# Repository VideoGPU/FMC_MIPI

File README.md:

# FMC_MIPI
FMC card to allow interfacing Xilinx FPGA boards with Jetson TX2 or TX1 via CSI-2 camera interface.
Made with KiCad.
Tested and works fine with KC705

HS and LP lanes come as a separate lines from FPGA.Switching between HS and LP modes is done using a high-speed switch 
TS3DDR3812.

## Some pictures:
Terminal output:

Example output:
The vertical line position in magenta strip indicates a frame number

The whole setup:

Interconnector board:

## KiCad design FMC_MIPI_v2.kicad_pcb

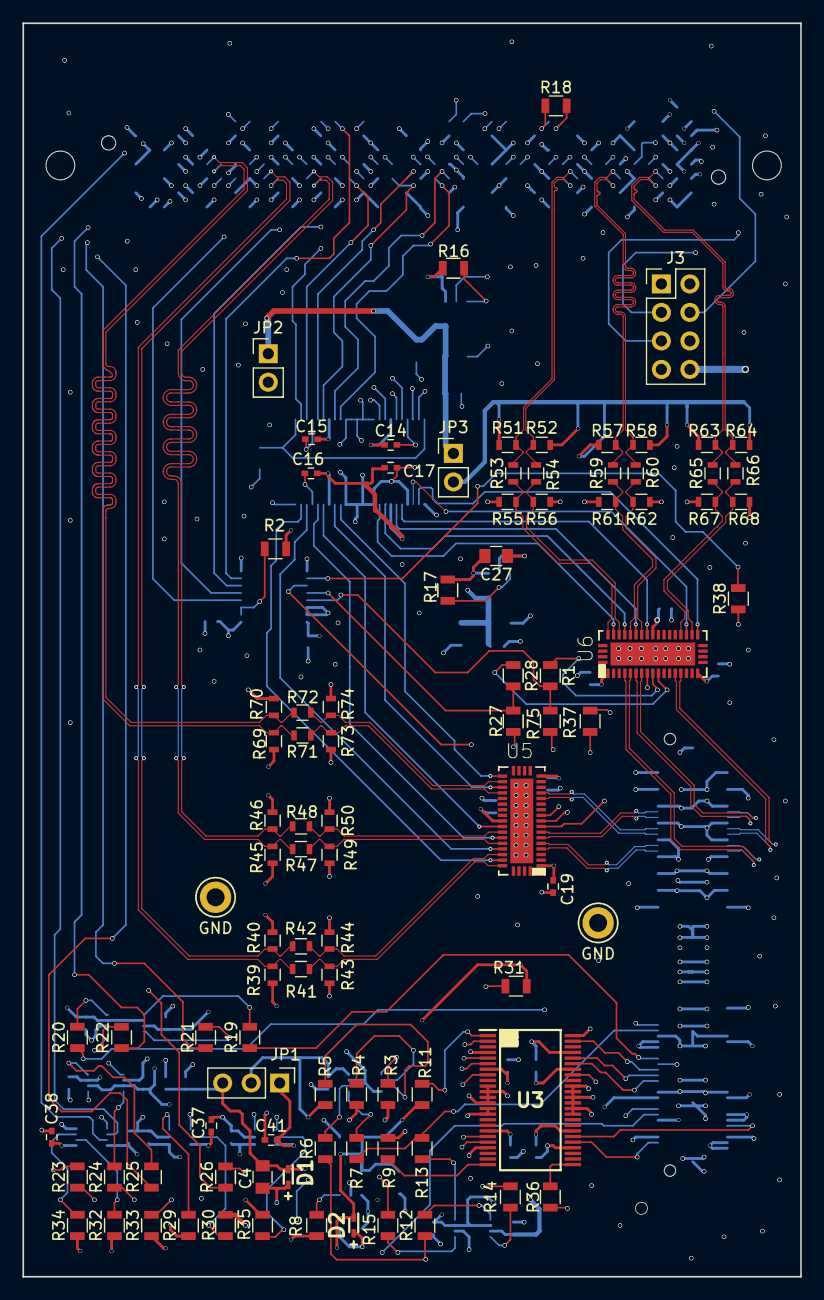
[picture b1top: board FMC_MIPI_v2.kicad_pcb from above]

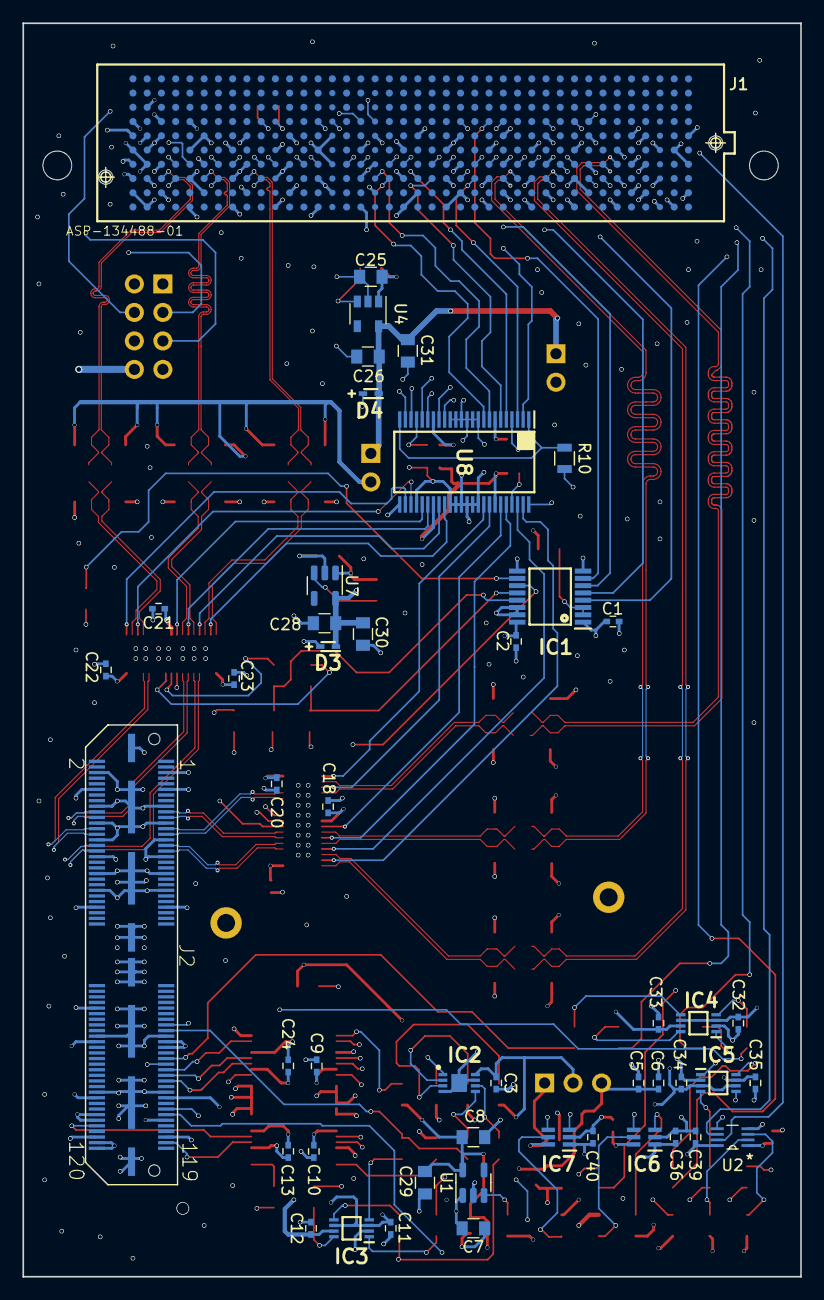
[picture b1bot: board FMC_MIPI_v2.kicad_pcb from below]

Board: 6 copper layers, 69.3 x 111.8 mm, 143 parts (48 on the bottom side), 156 nets.

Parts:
C1, C2, C3, C5, C6, C9, C10, C11, C12, C13, C14, C15, C16, C17, C18, C19, C20, C21, C22, C23, C24, C32, C33, C34, C35, C36, C37, C38, C39, C40, C41: 0.1uF; C_0402
C4, C29, C30, C31: 4.7uF; C_0805
C7, C8, C25, C26, C27, C28: 1uF; C_0805
D1, D2, D3, D4: UCLAMP0501H.TCT; SODFL1608X70N
IC1: SN74AVC4T245PWR; SOP65P640X120-16N
IC2: AT24MAC402-MAHM-T; SON50P300X200X60-9N
IC3, IC4, IC5: TCA9406DCUR; SOP50P310X90-8N
IC6, IC7: SN74AVC1T45DCKT; SOT65P210X110-6N
J1: ASP-134488-01; ASP-134488-01_VER2
J2: QTH-060-01-L-D-A; QTH-060-01-X-D-A-QTH-060-01-X-D-A
J3: Conn_01x08_Female; PinHeader_2x04_P2.54mm_Vertical
JP1: Jumper_3_Bridged12; Pin_Header_Straight_1x03_Pitch2.54mm
JP2, JP3: Jumper; Pin_Header_Straight_1x02_Pitch2.54mm
R1, R6, R7, R8, R12, R13, R14, R15, R16, R17, R18, R19, R20, R21, R22, R23, R24, R25, R26, R27, R28, R36, R37, R38, R75: 0; R_0805
R2, R3, R4, R5, R9, R10, R11, R30, R33, R35: 4.7k; R_0805
R29, R31, R32, R34: 2.2k; R_0805
R39, R40, R45, R46, R51, R52, R57, R58, R63, R64, R69, R70: 220; R_0603
R41, R42, R47, R48, R53, R54, R59, R60, R65, R66, R71, R72: 47; R_0603
R43, R44, R49, R50, R55, R56, R61, R62, R67, R68, R73, R74: 9.1; R_0603
TP1, TP2: GND; TestPoint_Keystone_5010-5014_Multipurpose
U1: LP5907MFX-1.8; SOT-23-5
U2: SN74AVC2T45DCUR
U3, U8: SN74AVCH16T245GR; SOP50P810X120-48N
U4: TLV75525PDBV; SOT-23-5
U5, U6: TS3DDR3812_RUA_42; TS3DDR3812RUAR
U7: LP5907MFX-1.2; SOT-23-5

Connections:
/FMC_Connector/DBG_IO_1: J1.G34 (LA31_N), J3.1
/FMC_Connector/DBG_IO_2: J1.G37 (LA33_N), J3.2
/FMC_Connector/DBG_IO_3: J1.G36 (LA33_P), J3.3
/FMC_Connector/DBG_IO_4: J1.G31 (LA29_N), J3.4
/FMC_Connector/DBG_IO_5: J1.D24 (LA23_N), J3.5
/FMC_Connector/DBG_IO_6: J1.D23 (LA23_P), J3.6
/FMC_Connector/TDI: J1.D30 (TDI), R18.1
/FMC_Connector/TDO: J1.D31 (TDO), R18.2
/Jetson_connector/EEPROM_A0: IC2.1 (A0), R3.1
/Jetson_connector/EEPROM_A1: IC2.2 (A1), R4.1
/Jetson_connector/EEPROM_A2: IC2.3 (A2), R5.1
/Jetson_connector/EEPROM_SCL: IC2.6 (SCL), R6.1
/Jetson_connector/EEPROM_SDA: IC2.5 (SDA), R7.1
/Jetson_connector/JT_VDD_1V2: J2.101 (DVDD_CAM_IO_1V2), R29.1
/Jetson_connector/JT_VDD_2V8: J2.81 (AVDD_CAM), J2.82 (AVDD_CAM), J2.83 (AVDD_CAM), R32.1
/Jetson_connector/JT_VDD_3V3: J2.108 (VDD_3V3_SLP1), J2.110 (VDD_3V3_SLP2), R34.1
/Jetson_connector/JT_VDD_5V: J2.109 (VDD_5V), J2.118 (VDD_5V), J2.120 (VDD_5V)
/Jetson_connector/VCC_1V8_EEPROM: C3.1, IC2.8 (VCC), JP1.2 (C), R5.2
/LVDS_to_Jetson_lines/CSI_LP_C_CLK_N: U5.24 (C8), U8.41 (1A5)
/LVDS_to_Jetson_lines/CSI_LP_C_CLK_P: U5.22 (C9), U8.40 (1A6)
/LVDS_to_Jetson_lines/CSI_LP_C_D0_N: U5.33 (C4), U8.44 (1A3)
/LVDS_to_Jetson_lines/CSI_LP_C_D0_P: U5.31 (C5), U8.43 (1A4)
/LVDS_to_Jetson_lines/CSI_LP_C_D1_N: U5.37 (C2), U8.47 (1A1)
/LVDS_to_Jetson_lines/CSI_LP_C_D1_P: U5.35 (C3), U8.46 (1A2)
/LVDS_to_Jetson_lines/CSI_LP_D_CLK_N: U6.24 (C8), U8.27 (2A7)
/LVDS_to_Jetson_lines/CSI_LP_D_CLK_P: U6.22 (C9), U8.26 (2A8)
/LVDS_to_Jetson_lines/CSI_LP_D_D0_N: U6.33 (C4), U8.30 (2A5)
/LVDS_to_Jetson_lines/CSI_LP_D_D0_P: U6.31 (C5), U8.29 (2A6)
/LVDS_to_Jetson_lines/CSI_LP_D_D1_N: U6.37 (C2), U8.33 (2A3)
/LVDS_to_Jetson_lines/CSI_LP_D_D1_P: U6.35 (C3), U8.32 (2A4)
/LVDS_to_Jetson_lines/DIR_IC1: IC1.2 (1DIR), IC1.3 (2DIR), R2.2
/LVDS_to_Jetson_lines/DIR_U8: R10.1, U8.1 (1DIR), U8.24 (2DIR)
/LVDS_to_Jetson_lines/EN_MIPI_OUT_CSI_C: IC1.11 (2B1), R37.2
/LVDS_to_Jetson_lines/EN_MIPI_OUT_CSI_D: IC1.10 (2B2), R38.2
/LVDS_to_Jetson_lines/EN_U5: R37.1, U5.8 (EN)
/LVDS_to_Jetson_lines/EN_U6: R38.1, U6.8 (EN)
/LVDS_to_Jetson_lines/HS_CSI_C_CLK_N: R71.1, R73.2, U5.25 (B8)
/LVDS_to_Jetson_lines/HS_CSI_C_CLK_P: R72.1, R74.1, U5.23 (B9)
/LVDS_to_Jetson_lines/HS_CSI_C_D0_N: R47.1, R49.2, U5.34 (B4)
/LVDS_to_Jetson_lines/HS_CSI_C_D0_P: R48.1, R50.1, U5.32 (B5)
/LVDS_to_Jetson_lines/HS_CSI_C_D1_N: R41.1, R43.2, U5.38 (B2)
/LVDS_to_Jetson_lines/HS_CSI_C_D1_P: R42.1, R44.1, U5.36 (B3)
/LVDS_to_Jetson_lines/HS_CSI_D_CLK_N: R65.1, R67.2, U6.25 (B8)
/LVDS_to_Jetson_lines/HS_CSI_D_CLK_P: R66.1, R68.1, U6.23 (B9)
/LVDS_to_Jetson_lines/HS_CSI_D_D0_N: R59.1, R61.2, U6.34 (B4)
/LVDS_to_Jetson_lines/HS_CSI_D_D0_P: R60.1, R62.1, U6.32 (B5)
/LVDS_to_Jetson_lines/HS_CSI_D_D1_N: R53.1, R55.2, U6.38 (B2)
/LVDS_to_Jetson_lines/HS_CSI_D_D1_P: R54.1, R56.1, U6.36 (B3)
/LVDS_to_Jetson_lines/SWITCH1_U5: R75.1, U5.9 (SEL1)
/LVDS_to_Jetson_lines/SWITCH1_U6: R1.1, U6.9 (SEL1)
/LVDS_to_Jetson_lines/SWITCH2_U5: R27.1, U5.10 (SEL2)
/LVDS_to_Jetson_lines/SWITCH2_U6: R28.1, U6.10 (SEL2)
/LVDS_to_Jetson_lines/SWITCH_CLOCK_LANES_CSI_CD: IC1.12 (1B2), R27.2, R28.2
/LVDS_to_Jetson_lines/SWITCH_DATA_LANES_CSI_CD: IC1.13 (1B1), R1.2, R75.2
/LVDS_to_Jetson_lines/VOLT_2P5_CSI_C: JP2.2, R39.1, R40.2, R45.1, R46.2, R69.1, R70.2
/LVDS_to_Jetson_lines/VOLT_2P5_CSI_D: JP3.2, R51.1, R52.2, R57.1, R58.2, R63.1, R64.2
/Slow_signals_level_shifters/1DIR_U3: R11.1, U3.1 (1DIR)
/Slow_signals_level_shifters/2DIR_U3: R9.1, U3.24 (2DIR)
/Slow_signals_level_shifters/ENN_JETSON_GPIO: IC7.4 (B), R36.2
/VDD_VADJ: C1.2, C9.1, C10.1, C12.1, C14.1, C15.1, C33.1, C35.1, C37.2, C39.2, C40.2, IC1.1 (VCCA), IC3.7 (VCCB), IC4.7 (VCCB), IC5.7 (VCCB), IC6.6 (VCCB), IC7.1 (VCCA), J1.E39 (VADJ), J1.F40 (VADJ), J1.G39 (VADJ), J1.H40 (VADJ), R2.1, R35.1, U2.8 (VCCB), U3.7 (VCCB_1), U3.18 (VCCB_2), U8.7 (VCCB_1), U8.18 (VCCB_2)
/VOLT_1P2: C16.1, C17.1, C28.2, C30.2, C36.2, D3.1, IC6.1 (VCCA), R30.1, U7.5 (OUT), U8.31 (VCCA_1), U8.42 (VCCA_2)
/VOLT_1P8: C8.2, C11.1, C13.1, C24.1, C29.2, C32.1, C34.1, C41.2, D2.1, IC3.3 (VCCA), IC3.6 (OE), IC4.3 (VCCA), IC4.6 (OE), IC5.3 (VCCA), IC5.6 (OE), IC7.6 (VCCB), JP1.1 (A), R11.2, U1.5 (OUT), U3.31 (VCCA_1), U3.42 (VCCA_2)
/VOLT_2P5: C26.2, C31.2, D4.1, JP2.1, JP3.1, U4.5 (OUT)
/VOLT_3P3: C2.2, C7.2, C18.2, C19.2, C20.2, C21.2, C22.2, C23.2, C25.2, C27.2, C38.2, IC1.16 (VCCB), J1.C39 (3PV3), J1.D36 (3P3V), J1.D38 (3P3V), J1.D40 (3P3V), R8.1, R16.1, R17.1, R33.1, U1.1 (IN), U2.1 (VCCA), U4.1 (IN), U5.1 (VCC), U5.17 (VCC), U5.30 (VCC), U6.1 (VCC), U6.17 (VCC), U6.30 (VCC), U7.1 (IN)
CSI_C_CLK_N: J2.27 (CSI2_CLK–), U5.13 (A8)
CSI_C_CLK_P: J2.25 (CSI2_CLK+), U5.14 (A9)
CSI_C_D0_N: J2.21 (CSI2_D0–), U5.6 (A4)
CSI_C_D0_P: J2.19 (CSI2_D0+), U5.7 (A5)
CSI_C_D1_N: J2.33 (CSI2_D1–), U5.4 (A2)
CSI_C_D1_P: J2.31 (CSI2_D1+), U5.5 (A3)
CSI_D_CLK_N: J2.28 (CSI3_CLK–), U6.13 (A8)
CSI_D_CLK_P: J2.26 (CSI3_CLK+), U6.14 (A9)
CSI_D_D0_N: J2.22 (CSI3_D0–), U6.6 (A4)
CSI_D_D0_P: J2.20 (CSI3_D0+), U6.7 (A5)
CSI_D_D1_N: J2.34 (CSI3_D1–), U6.4 (A2)
CSI_D_D1_P: J2.32 (CSI3_D1+), U6.5 (A3)
Earth: C1.1, C2.1, C3.2, C4.1, C5.1, C6.1, C7.1, C8.1, C9.2, C10.2, C11.2, C12.2, C13.2, C14.2, C15.2, C16.2, C17.2, C18.1, C19.1, C20.1, C21.1, C22.1, C23.1, C24.2, C25.1, C26.1, C27.1, C28.1, C29.1, C30.1, C31.1, C32.2, C33.2, C34.2, C35.2, C36.1, C37.1, C38.1, C39.1, C40.1, C41.1, D1.2, D2.2, D3.2, D4.2, IC1.8 (GND), IC1.9 (GND), IC1.14 (2~OE), IC1.15 (1~OE), IC2.4 (GND), IC2.7 (WP), IC2.9 (EP), IC3.2 (GND), IC4.2 (GND), IC5.2 (GND), IC6.2 (GND), IC7.2 (GND), J1.E1 (GND), J1.E4 (GND), J1.E5 (GND), J1.E8 (GND), J1.E11 (GND), J1.E14 (GND), J1.E17 (GND), J1.E20 (GND), J1.E23 (GND), J1.E26 (GND), J1.E29 (GND), J1.E32 (GND), J1.E35 (GND), J1.E38 (GND), J1.E40 (GND), J1.F2 (GND), J1.F3 (GND), J1.F6 (GND), J1.F9 (GND), J1.F12 (GND), J1.F15 (GND), J1.F18 (GND), J1.F21 (GND), J1.F24 (GND), J1.F27 (GND), J1.F30 (GND), J1.F33 (GND), J1.F36 (GND), J1.F39 (GND), J1.G1 (GND), J1.G4 (GND), J1.G5 (GND), J1.G8 (GND), J1.G11 (GND), J1.G14 (GND), J1.G17 (GND), J1.G23 (GND), J1.G26 (GND), J1.G29 (GND), J1.G32 (GND), J1.G35 (GND), J1.G38 (GND), J1.G40 (GND), J1.H3 (GND), J1.H6 (GND), J1.H9 (GND), J1.H12 (GND), J1.H15 (GND), J1.H18 (GND), J1.H21 (GND), J1.H24 (GND), J1.H27 (GND), J1.H30 (GND), J1.H33 (GND), J1.H36 (GND), J1.H39 (GND), J1.J1 (GND), J1.J4 (GND), J1.J5 (GND), J1.J8 (GND), J1.J11 (GND), J1.J14 (GND), J1.J17 (GND), J1.J20 (GND), J1.J23 (GND), J1.J26 (GND), J1.J29 (GND), J1.J32 (GND), J1.J35 (GND), J1.J38 (GND), J1.J40 (GND), J1.K2 (GND), J1.K3 (GND), J1.K6 (GND), J1.K9 (GND), J1.K12 (GND), J1.K15 (GND), J1.K18 (GND), J1.K21 (GND), J1.K24 (GND), J1.K27 (GND), J1.K30 (GND), J1.K33 (GND), J1.K36 (GND), J1.K39 (GND), J2.5 (GND), J2.6 (GND), J2.11 (GND), J2.12 (GND), J2.17 (GND), J2.18 (GND), J2.23 (GND), J2.24 (GND), J2.29 (GND), J2.30 (GND), J2.35 (GND), J2.36 (GND), J2.41 (GND), J2.42 (GND), J2.47 (GND), J2.48 (GND), J2.53 (GND), J2.54 (GND), J2.70 (GND), J2.79 (GND), J2.80 (GND), J2.99 (GND), J2.100 (GND), J2.115 (GND), J2.116 (GND), J2.G1, J2.G2, J2.G3, J2.G4, J2.G5, J2.G6, J2.G7, J2.G8, J3.7, J3.8, R3.2, R4.2, R9.2, R10.2, R43.1, R44.2, R49.1, R50.2, R55.1, R56.2, R61.1, R62.2, R67.1, R68.2, R73.1, R74.2, TP1.1, TP2.1, U1.2 (GND), U2.4 (GND), U3.4 (GND_1), U3.10 (GND_2), U3.11 (1B7), U3.12 (1B8), U3.13 (2B1), U3.14 (2B2), U3.15 (GND_3), U3.21 (GND_4), U3.28 (GND_5), U3.34 (GND_6), U3.35 (2A2), U3.36 (2A1), U3.37 (1A8), U3.38 (1A7), U3.39 (GND_7), U3.45 (GND_8), U3.48 (1~OE), U4.2 (GND), U5.43 (EPAD), U6.43 (EPAD), U7.2 (GND), U8.4 (GND_1), U8.10 (GND_2), U8.11 (1B7), U8.12 (1B8), U8.13 (2B1), U8.14 (2B2), U8.15 (GND_3), U8.21 (GND_4), U8.25 (2~OE), U8.28 (GND_5), U8.34 (GND_6), U8.35 (2A2), U8.36 (2A1), U8.37 (1A8), U8.38 (1A7), U8.39 (GND_7), U8.45 (GND_8), U8.48 (1~OE)
FMC_1P2V_MONITOR: IC6.4 (B), J1.H8 (LA02_N)
FMC_1P8V_MONITOR: J1.G27 (LA25_P), U3.8 (1B5)
FMC_2P8V_MONITOR: J1.D8 (LA01_P_CC), U2.7 (B1)
FMC_3P3V_MONITOR: J1.D9 (LA01_N_CC), U2.6 (B2)
FMC_CAM0_MCLK: J1.G33 (LA31_P), U3.2 (1B1)
FMC_CAM0_PWR: J1.G30 (LA29_P), U3.5 (1B3)
FMC_CAM0_RST: J1.G28 (LA25_N), U3.6 (1B4)
FMC_CSI_LP_C_CLK_N: J1.H23 (LA19_N), U8.8 (1B5)
FMC_CSI_LP_C_CLK_P: J1.H22 (LA19_P), U8.9 (1B6)
FMC_CSI_LP_C_D0_N: J1.H20 (LA15_N), U8.5 (1B3)
FMC_CSI_LP_C_D0_P: J1.H19 (LA15_P), U8.6 (1B4)
FMC_CSI_LP_C_D1_N: J1.H17 (LA11_N), U8.2 (1B1)
FMC_CSI_LP_C_D1_P: J1.H16 (LA11_P), U8.3 (1B2)
FMC_CSI_LP_D_CLK_N: J1.G22 (LA20_N), U8.22 (2B7)
FMC_CSI_LP_D_CLK_P: J1.G21 (LA20_P), U8.23 (2B8)
FMC_CSI_LP_D_D0_N: J1.G19 (LA16_N), U8.19 (2B5)
FMC_CSI_LP_D_D0_P: J1.G18 (LA16_P), U8.20 (2B6)
FMC_CSI_LP_D_D1_N: J1.G16 (LA12_N), U8.16 (2B3)
FMC_CSI_LP_D_D1_P: J1.G15 (LA12_P), U8.17 (2B4)
FMC_ENN_JT_GPIO_INPUT: IC7.3 (A), J1.D17 (LA13_P)
FMC_EN_MIPI_OUT_CLOCK_VADJ: IC1.7 (2A2), J1.D15 (LA09_N)
FMC_EN_MIPI_OUT_DATA_VADJ: IC1.6 (2A1), J1.D14 (LA09_P)
FMC_GPIO9_OUT: J1.D27 (LA26_N), U3.19 (2B5)
FMC_GPIO17_OUT: J1.D26 (LA26_P), U3.20 (2B6)
FMC_HS_CSI_C_CLK_N: J1.G7 (LA00_N_CC), R69.2, R71.2
FMC_HS_CSI_C_CLK_P: J1.G6 (LA00_P_CC), R70.1, R72.2
FMC_HS_CSI_C_D0_N: J1.H14 (LA07_N), R45.2, R47.2
FMC_HS_CSI_C_D0_P: J1.H13 (LA07_P), R46.1, R48.2
FMC_HS_CSI_C_D1_N: J1.H11 (LA04_N), R39.2, R41.2
FMC_HS_CSI_C_D1_P: J1.H10 (LA04_P), R40.1, R42.2
FMC_HS_CSI_D_CLK_N: J1.H38 (LA32_N), R63.2, R65.2
FMC_HS_CSI_D_CLK_P: J1.H37 (LA32_P), R64.1, R66.2
FMC_HS_CSI_D_D0_N: J1.H35 (LA30_N), R57.2, R59.2
FMC_HS_CSI_D_D0_P: J1.H34 (LA30_P), R58.1, R60.2
FMC_HS_CSI_D_D1_N: J1.H32 (LA28_N), R51.2, R53.2
FMC_HS_CSI_D_D1_P: J1.H31 (LA28_P), R52.1, R54.2
FMC_I2C2_CAM_CLK: J1.G9 (LA03_P), R21.2
FMC_I2C2_CAM_DAT: J1.D11 (LA05_P), R22.2
FMC_I2C3_CAM_CLK: J1.H7 (LA02_P), R25.2
FMC_I2C3_CAM_DAT: J1.G10 (LA03_N), R26.2
FMC_I2C_CAM_CLK: J1.G25 (LA22_N), R14.2
FMC_I2C_CAM_DAT: J1.G24 (LA22_P), R15.2
FMC_SWITCH_CLOCK_LANES_VADJ: IC1.5 (1A2), J1.G13 (LA08_N)
FMC_SWITCH_DATA_LANES_VADJ: IC1.4 (1A1), J1.G12 (LA08_P)
JT_1p8V_CAM0_MCLK: J2.91 (CAM0_MCLK), U3.47 (1A1)
JT_1p8V_CAM0_PWR: J2.93 (GPIO0_CAM0_PWR), U3.44 (1A3)
JT_1p8V_CAM0_RST: J2.95 (GPIO2_CAM0_RST), U3.43 (1A4)
JT_1p8V_GPIO9_IN: J2.112, U3.30 (2A5)
JT_1p8V_GPIO17_IN: J2.117 (CAM_INTR), U3.29 (2A6)
JT_1p8V_I2C2_CAM_CLK: J2.87 (CAM_I2C2_SCL), R19.1
JT_1p8V_I2C2_CAM_DAT: J2.89 (CAM_I2C2_SDA), R20.1
JT_1p8V_I2C3_CAM_CLK: J2.105 (I2C_GP0_CLK_1V8), R23.1
JT_1p8V_I2C3_CAM_DAT: J2.107 (I2C_GP0_DAT_1V8), R24.1
JT_1p8V_I2C_CAM_CLK: J2.75 (I2C_CAM_CLK), R6.2, R12.1
JT_1p8V_I2C_CAM_DAT: J2.77 (I2C_CAM_DAT), R7.2, R13.1
JT_VDD_1V8: C4.2, C5.2, C6.2, D1.1, J2.102 (DVDD_CAM_IO_1V8), JP1.3 (B), R31.2
unnamed: IC3.1 (SDA_B), R15.1
unnamed: IC3.4 (SDA_A), R13.2
unnamed: IC3.5 (SCL_A), R12.2
unnamed: IC3.8 (SCL_B), R14.1
unnamed: IC4.1 (SDA_B), R22.1
unnamed: IC4.4 (SDA_A), R20.2
unnamed: IC4.5 (SCL_A), R19.2
unnamed: IC4.8 (SCL_B), R21.1
unnamed: IC5.1 (SDA_B), R26.1
unnamed: IC5.4 (SDA_A), R24.2
unnamed: IC5.5 (SCL_A), R23.2
unnamed: IC5.8 (SCL_B), R25.1
unnamed: IC6.3 (A), R29.2
unnamed: IC6.5 (DIR), R30.2
unnamed: IC7.5 (DIR), R35.2
unnamed: R8.2, U1.3 (EN)
unnamed: R16.2, U4.3 (EN)
unnamed: R17.2, U7.3 (EN)
unnamed: R31.1, U3.41 (1A5)
unnamed: R32.2, U2.2 (A1)
unnamed: R33.2, U2.5 (DIR)
unnamed: R34.2, U2.3 (A2)
unnamed: R36.1, U3.25 (2~OE)

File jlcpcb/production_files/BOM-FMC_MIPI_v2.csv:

Comment,Designator,Footprint,LCSC
9.1,"R43,R44,R49,R50,R55,R56,R61,R62,R67,R68,R73,R74",R_0603,C103890
220,"R39,R40,R45,R46,R51,R52,R57,R58,R63,R64,R69,R70",R_0603,C107696
47,"R41,R42,R47,R48,R53,R54,R59,R60,R65,R66,R71,R72",R_0603,C114623
UCLAMP0501H.TCT,"D1,D2,D3,D4",SODFL1608X70N,C117557
SN74AVC2T45DCUR,U2,SN74AVC2T45DCUR,C140318
0.1uF,"C1,C10,C11,C12,C13,C14,C15,C16,C17,C18,C19,C2,C20,C21,C22,C23,C24,C3,C32,C33,C34,C35,C36,C37,C38,C39,C40,C41,C5,C6,C9",C_0402,C1525
0,"R1,R12,R13,R14,R15,R16,R17,R18,R19,R20,R21,R22,R23,R24,R25,R26,R27,R28,R36,R37,R38,R6,R7,R75,R8",R_0805,C17477
2.2k,"R29,R31,R32,R34",R_0805,C17520
4.7k,"R10,R11,R2,R3,R30,R33,R35,R4,R5,R9",R_0805,C17673
4.7uF,"C29,C30,C31,C4",C_0805,C1779
TS3DDR3812_RUA_42,"U5,U6",TS3DDR3812RUAR,C181266
SN74AVCH16T245GR,"U3,U8",SOP50P810X120-48N,C181413
AT24MAC402-MAHM-T,IC2,SON50P300X200X60-9N,C2061210
SN74AVC1T45DCKT,"IC6,IC7",SOT65P210X110-6N,C2677669
ASP-134488-01,J1,ASP-134488-01_VER2,C2762238
1uF,"C25,C26,C27,C28,C7,C8",C_0805,C28323
TLV75525PDBV,U4,SOT-23-5,C2867155
QTH-060-01-L-D-A,J2,QTH-060-01-X-D-A-QTH-060-01-X-D-A,C3640977
LP5907MFX-1.2,U7,SOT-23-5,C73478
SN74AVC4T245PWR,IC1,SOP65P640X120-16N,C81461
TCA9406DCUR,"IC3,IC4,IC5",SOP50P310X90-8N,C840107
LP5907MFX-1.8,U1,SOT-23-5,C92498
Jumper_3_Bridged12,JP1,Pin_Header_Straight_1x03_Pitch2.54mm,
Jumper,JP2,Pin_Header_Straight_1x02_Pitch2.54mm,
Jumper,JP3,Pin_Header_Straight_1x02_Pitch2.54mm,
GND,TP1,TestPoint_Keystone_5010-5014_Multipurpose,
Conn_01x08_Female,J3,PinHeader_2x04_P2.54mm_Vertical,
GND,TP2,TestPoint_Keystone_5010-5014_Multipurpose,

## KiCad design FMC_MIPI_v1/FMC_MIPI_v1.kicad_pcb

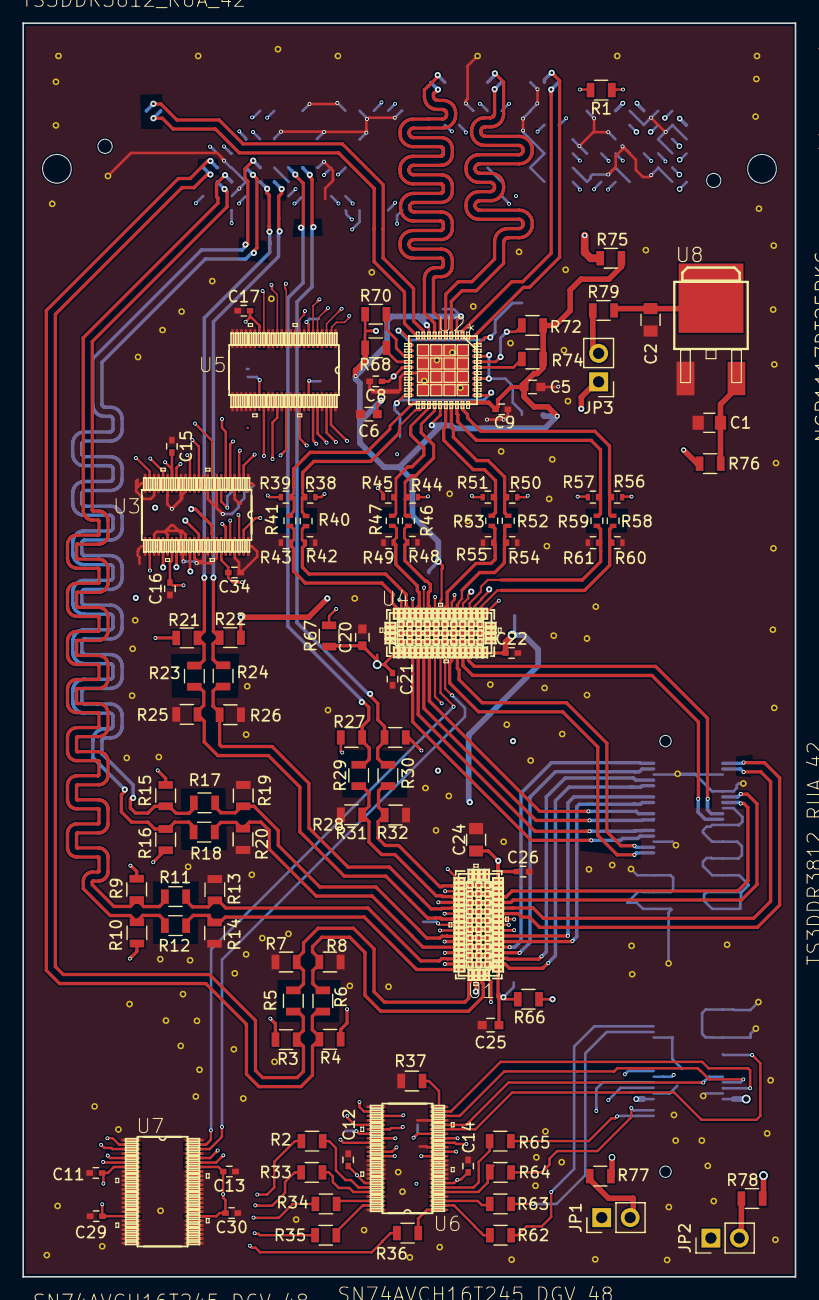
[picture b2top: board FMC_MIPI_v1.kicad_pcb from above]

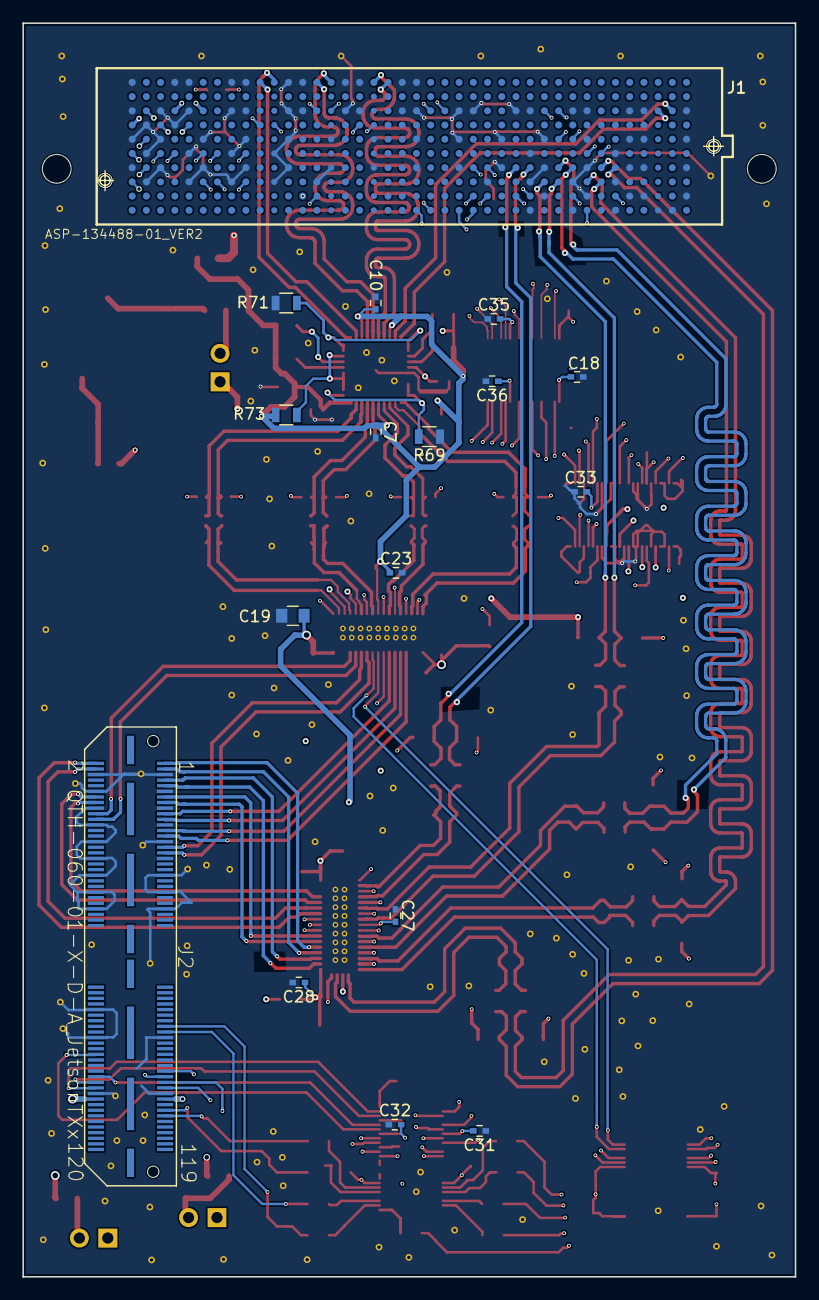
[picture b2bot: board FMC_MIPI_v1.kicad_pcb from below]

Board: 6 copper layers, 69.0 x 112.0 mm, 126 parts (17 on the bottom side), 167 nets.

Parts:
C1, C2, C19, C24: 10uF; C_0805
C5, C6, C20, C25: 1uF; C_0603
C7, C8, C9, C10, C11, C12, C13, C14, C15, C16, C17, C18, C21, C22, C23, C26, C27, C28, C29, C30, C31, C32, C33, C34, C35, C36: 0.1uF; C_0402
J1: ASP-134488-01_VER2; hdmi3dmix-ASP-134488-01_VER2
J2: QTH-060-01-X-D-A_JetsonTXx; QTH-060-01-X-D-A-QTH-060-01-X-D-A
JP1, JP2, JP3: Jumper; Pin_Header_Straight_1x02_Pitch2.54mm
R1, R2, R33, R34, R35, R36, R37, R62, R63, R64, R65, R66, R67, R75, R76, R77, R78, R79: 0k; R_0805
R3, R4, R9, R10, R15, R16, R21, R22, R27, R28: 220; R_0805
R5, R6, R11, R12, R17, R18, R23, R24, R29, R30: 47; R_0805
R7, R8, R13, R14, R19, R20, R25, R26, R31, R32: 12; R_0805
R38, R39, R44, R45, R50, R51, R56, R57: 220; R_0402
R40, R41, R46, R47, R52, R53, R58, R59: 47; R_0402
R42, R43, R48, R49, R54, R55, R60, R61: 12; R_0402
R68, R70, R72, R73, R74: 4.7k; R_0805
R69, R71: 2.2k; R_0805
U1, U4: TS3DDR3812_RUA_42; TS3DDR3812RUAR
U2: DS25BR440_RTA_40; DS25BR440_SQA40A
U3, U5, U6, U7: SN74AVCH16T245_DGV_48; hdmi3dmix-DGV48
U8: NCP1117DT25RKG; hdmi3dmix-DPAK-3

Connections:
/CAM0_MCLK: J2.91, U6.13
/CAM0_PWR: J2.93, U6.14
/CAM0_RST: J2.95, U6.16
/CAM2_MCLK: J2.94, U6.20
/CAM2_PWRD: J2.96, U6.22
/CAM2_RST: J2.98, U6.23
/CAM_FLASH_EN: J2.97, U6.17
/CAM_VSYNC: J2.86, U6.19
/CML_to_DPHY/DS25_EQ0: R71.2, U2.11, U2.12, U2.39, U2.40
/CML_to_DPHY/DS25_PE0: R69.2, U2.18, U2.19, U2.20, U2.31
/CML_to_DPHY/LP2_CLK_N: U4.35, U5.35
/CML_to_DPHY/LP2_CLK_P: U4.37, U5.32
/CML_to_DPHY/LP2_D0_N: U4.31, U5.40
/CML_to_DPHY/LP2_D0_P: U4.33, U5.37
/CML_to_DPHY/LP2_D1_N: U4.26, U5.44
/CML_to_DPHY/LP2_D1_P: U4.28, U5.43
/CML_to_DPHY/LP2_D2_N: U4.22, U5.47
/CML_to_DPHY/LP2_D2_P: U4.24, U5.46
/CML_to_DPHY/LVDS_2_SLVS_0603_CLK/LVDS_IN_N: R39.1, R41.2, U2.21
/CML_to_DPHY/LVDS_2_SLVS_0603_CLK/LVDS_IN_P: R38.1, R40.2, U2.22
/CML_to_DPHY/LVDS_2_SLVS_0603_D0/LVDS_IN_N: R45.1, R47.2, U2.23
/CML_to_DPHY/LVDS_2_SLVS_0603_D0/LVDS_IN_P: R44.1, R46.2, U2.24
/CML_to_DPHY/LVDS_2_SLVS_0603_D1/LVDS_IN_N: R51.1, R53.2, U2.26
/CML_to_DPHY/LVDS_2_SLVS_0603_D1/LVDS_IN_P: R50.1, R52.2, U2.27
/CML_to_DPHY/LVDS_2_SLVS_0603_D2/LVDS_IN_N: R57.1, R59.2, U2.28
/CML_to_DPHY/LVDS_2_SLVS_0603_D2/LVDS_IN_P: R56.1, R58.2, U2.29
/CML_to_DPHY/SLVS2_CLK_N: R41.1, R43.1, U4.38
/CML_to_DPHY/SLVS2_CLK_P: R40.1, R42.1, U4.36
/CML_to_DPHY/SLVS2_D0_N: R47.1, R49.1, U4.34
/CML_to_DPHY/SLVS2_D0_P: R46.1, R48.1, U4.32
/CML_to_DPHY/SLVS2_D1_N: R53.1, R55.1, U4.29
/CML_to_DPHY/SLVS2_D1_P: R52.1, R54.1, U4.27
/CML_to_DPHY/SLVS2_D2_N: R59.1, R61.1, U4.25
/CML_to_DPHY/SLVS2_D2_P: R58.1, R60.1, U4.23
/FMC_I2C_CAM_CLK_R: R35.1, U6.47
/FMC_I2C_CAM_DAT_R: R34.1, U6.46
/FMC_I2C_GP0_CLK_1V8_R: R33.1, U6.44
/FMC_I2C_GP0_DAT_1V8_R: R2.1, U6.43
/I2C_CAM_CLK: J2.75, R62.1
/I2C_CAM_CLK_R: R62.2, U6.2
/I2C_CAM_DAT: J2.77, R63.1
/I2C_CAM_DAT_R: R63.2, U6.3
/I2C_GP0_CLK_1V8: J2.105, R64.1
/I2C_GP0_CLK_1V8_R: R64.2, U6.5
/I2C_GP0_DAT_1V8: J2.107, R65.1
/I2C_GP0_DAT_1V8_R: R65.2, U6.6
/JETSON_1V2: J2.101, R77.1
/JETSON_1V8: J2.102, R78.2
/LVDS_to_DPHY/FMC_VOLT_3P3_R: J1.C39, J1.D36, J1.D38, J1.D40, R75.2
/LVDS_to_DPHY/FMC_VOLT_12P0_R: J1.C35, J1.C37, R76.2
/LVDS_to_DPHY/LA14_N: J1.C19, U3.17
/LVDS_to_DPHY/LA14_P: J1.C18, U3.14
/LVDS_to_DPHY/LA23_N: J1.D24, U3.12
/LVDS_to_DPHY/LA23_P: J1.D23, U3.9
/LVDS_to_DPHY/LA27_N: J1.C27, U3.2
/LVDS_to_DPHY/LA27_P: J1.C26, U3.3
/LVDS_to_DPHY/LP_CLK_N: U1.42, U3.26
/LVDS_to_DPHY/LP_CLK_P: U1.40, U3.29
/LVDS_to_DPHY/LP_D0_N: U1.37, U3.32
/LVDS_to_DPHY/LP_D0_P: U1.35, U3.35
/LVDS_to_DPHY/LP_D1_N: U1.33, U3.37
/LVDS_to_DPHY/LP_D1_P: U1.31, U3.40
/LVDS_to_DPHY/LP_D2_N: U1.28, U3.43
/LVDS_to_DPHY/LP_D2_P: U1.26, U3.44
/LVDS_to_DPHY/LP_D3_N: U1.24, U3.46
/LVDS_to_DPHY/LP_D3_P: U1.22, U3.47
/LVDS_to_DPHY/SLVS_HS_CLK_N: R6.1, R8.1, U1.41
/LVDS_to_DPHY/SLVS_HS_CLK_P: R5.1, R7.1, U1.39
/LVDS_to_DPHY/SLVS_HS_D0_N: R12.1, R14.1, U1.38
/LVDS_to_DPHY/SLVS_HS_D0_P: R11.1, R13.1, U1.36
/LVDS_to_DPHY/SLVS_HS_D1_N: R18.1, R20.1, U1.34
/LVDS_to_DPHY/SLVS_HS_D1_P: R17.1, R19.1, U1.32
/LVDS_to_DPHY/SLVS_HS_D2_N: R24.1, R26.1, U1.27
/LVDS_to_DPHY/SLVS_HS_D2_P: R23.1, R25.1, U1.29
/LVDS_to_DPHY/SLVS_HS_D3_N: R30.1, R32.1, U1.23
/LVDS_to_DPHY/SLVS_HS_D3_P: R29.1, R31.1, U1.25
/LVDS_to_DPHY/TDI: J1.D30, R1.2
/LVDS_to_DPHY/TDO: J1.D31, R1.1
/VOLT_2P5_R: C2.1, R79.2, U8.2
DP0_C2M_N: J1.C3, U2.10
DP0_C2M_P: J1.C2, U2.9
DP1_C2M_N: J1.A23, U2.7
DP1_C2M_P: J1.A22, U2.6
DP2_C2M_N: J1.A27, U2.5
DP2_C2M_P: J1.A26, U2.4
DP3_C2M_N: J1.A31, U2.2
DP3_C2M_P: J1.A30, U2.1
DVDD_CAM_IO_1V2: C16.2, C18.1, C34.2, C36.1, JP1.1, U3.31, U3.42, U5.31, U5.42
DVDD_CAM_IO_1V8: C14.2, C32.2, JP2.1, U6.7, U6.18
Earth: C1.2, C2.2, C5.2, C6.2, C7.2, C8.2, C9.2, C10.2, C11.1, C12.1, C13.1, C14.1, C15.1, C16.1, C17.1, C18.2, C19.2, C20.2, C21.2, C22.2, C23.2, C24.2, C25.2, C26.2, C27.2, C28.2, C29.1, C30.1, C31.1, C32.1, C33.1, C34.1, C35.1, C36.2, J1.A20, J1.A21, J1.A24, J1.A25, J1.A28, J1.A29, J1.A32, J1.A33, J1.A36, J1.A37, J1.A40, J1.C1, J1.C4, J1.C5, J1.C8, J1.C9, J1.C12, J1.C13, J1.C16, J1.C17, J1.C20, J1.C21, J1.C24, J1.C25, J1.C28, J1.C29, J1.C32, J1.C33, J1.C36, J1.C38, J1.C40, J1.D37, J1.D39, J1.E1, J1.E4, J1.E5, J1.E8, J1.E11, J1.E14, J1.E17, J1.E20, J1.E23, J1.E26, J1.E29, J1.E32, J1.E35, J1.E38, J1.E40, J1.F6, J1.F12, J1.F30, J1.F33, J1.F36, J1.F39, J1.G1, J1.G4, J1.G5, J1.G8, J1.G11, J1.G14, J1.G17, J1.G20, J1.G23, J1.G26, J1.G29, J1.G32, J1.G35, J1.G38, J1.G40, J1.H6, J1.H9, J1.H12, J1.H15, J1.H27, J1.H30, J1.H33, J1.H36, J1.H39, J1.J1, J1.J4, J1.J5, J1.J8, J1.J11, J1.K2, J1.K3, J1.K6, J1.K9, J1.K12, J2.5, J2.6, J2.11, J2.12, J2.17, J2.18, J2.23, J2.24, J2.29, J2.30, J2.35, J2.36, J2.41, J2.42, J2.47, J2.48, J2.53, J2.54, J2.70, J2.79, J2.80, J2.99, J2.100, R7.2, R8.2, R13.2, R14.2, R19.2, R20.2, R25.2, R26.2, R31.2, R32.2, R37.1, R42.2, R43.2, R48.2, R49.2, R54.2, R55.2, R60.2, R61.2, R69.1, R71.1, U1.43, U1.V, U1.V_1, U1.V_2, U1.V_3, U1.V_4, U1.V_5, U1.V_6, U1.V_7, U1.V_8, U1.V_9, U1.V_10, U1.V_11, U1.V_12, U1.V_13, U1.V_14, U1.V_15, U1.V_16, U1.V_17, U2.16, U2.41, U3.1, U3.4, U3.8, U3.10, U3.11, U3.13, U3.15, U3.16, U3.19, U3.21, U3.22, U3.24, U3.25, U3.27, U3.28, U3.30, U3.33, U3.34, U3.36, U3.38, U3.39, U3.41, U3.45, U3.48, U4.43, U4.V, U4.V_1, U4.V_2, U4.V_3, U4.V_4, U4.V_5, U4.V_6, U4.V_7, U4.V_8, U4.V_9, U4.V_10, U4.V_11, U4.V_12, U4.V_13, U4.V_14, U4.V_15, U4.V_16, U4.V_17, U5.1, U5.4, U5.8, U5.10, U5.11, U5.13, U5.15, U5.16, U5.19, U5.20, U5.21, U5.22, U5.23, U5.24, U5.25, U5.26, U5.27, U5.28, U5.29, U5.30, U5.33, U5.34, U5.36, U5.38, U5.39, U5.41, U5.45, U5.48, U6.4, U6.8, U6.9, U6.10, U6.11, U6.12, U6.15, U6.21, U6.25, U6.28, U6.34, U6.37, U6.38, U6.39, U6.40, U6.41, U6.45, U6.48, U7.1, U7.4, U7.8, U7.9, U7.10, U7.11, U7.12, U7.13, U7.14, U7.15, U7.16, U7.17, U7.19, U7.20, U7.21, U7.22, U7.23, U7.24, U7.25, U7.26, U7.27, U7.28, U7.29, U7.30, U7.32, U7.33, U7.34, U7.35, U7.36, U7.37, U7.38, U7.39, U7.40, U7.41, U7.45, U7.48, U8.1
FMC_CAM0_MCLK: J1.F32, U6.36
FMC_CAM0_PWR: J1.H32, U6.35
FMC_CAM0_RST: J1.H34, U6.33
FMC_CAM2_MCLK: J1.F35, U6.29
FMC_CAM2_PWRD: J1.F37, U6.27
FMC_CAM2_RST: J1.F38, U6.26
FMC_CAM_FLASH_EN: J1.H35, U6.32
FMC_CAM_VSYNC: J1.F34, U6.30
FMC_I2C_CAM_CLK: J1.F7, R35.2
FMC_I2C_CAM_DAT: J1.J6, R34.2
FMC_I2C_GP0_CLK_1V8: J1.K8, R33.2
FMC_I2C_GP0_DAT_1V8: J1.J9, R2.2
FMC_LA02_N: J1.H8, R10.1, R12.2
FMC_LA02_P: J1.H7, R9.1, R11.2
FMC_LA03_N: J1.G10, R16.1, R18.2
FMC_LA03_P: J1.G9, R15.1, R17.2
FMC_LA04_N: J1.H11, R22.1, R24.2
FMC_LA04_P: J1.H10, R21.1, R23.2
FMC_LA08_N: J1.G13, R28.1, R30.2
FMC_LA08_P: J1.G12, R27.1, R29.2
FMC_LP2_CLK_N: J1.J13, U5.14
FMC_LP2_CLK_P: J1.J12, U5.17
FMC_LP2_D0_N: J1.G16, U5.9
FMC_LP2_D0_P: J1.G15, U5.12
FMC_LP2_D1_N: J1.J16, U5.5
FMC_LP2_D1_P: J1.J15, U5.6
FMC_LP2_D2_N: J1.K16, U5.2
FMC_LP2_D2_P: J1.K17, U5.3
FMC_LP_CLK_N: J1.K20, U3.23
FMC_LP_CLK_P: J1.K19, U3.20
FMC_LP_D2_N: J1.J28, U3.6
FMC_LP_D2_P: J1.J27, U3.5
FMC_Switch1_SEL1: J1.C10, U7.5
FMC_Switch1_SEL2: J1.C11, U7.6
FMC_Switch2_SEL1: J1.E9, U7.2
FMC_Switch2_SEL2: J1.E10, U7.3
FMC_TR_1DIR: J1.F8, R36.1
FMC_VADJ: C11.2, C12.2, C15.2, C17.2, C29.2, C31.2, C33.2, C35.2, J1.E39, J1.F40, J1.G39, J1.H40, U3.7, U3.18, U5.7, U5.18, U6.31, U6.42, U7.7, U7.18
FMC_VOLT_3P3: C5.1, C6.1, C7.1, C8.1, C9.1, C10.1, C13.2, C19.1, C20.1, C21.1, C22.1, C23.1, C24.1, C25.1, C26.1, C27.1, C28.1, C30.2, R66.1, R67.1, R68.1, R70.1, R72.2, R73.2, R74.2, R75.1, U1.1, U1.17, U1.30, U2.3, U2.8, U2.15, U2.25, U2.30, U4.1, U4.17, U4.30, U7.31, U7.42
FMC_VOLT_12P0: C1.1, R76.1, U8.3
LA00_CC_N: J1.G7, R4.1, R6.2
LA00_CC_P: J1.G6, R3.1, R5.2
MUXED1_CLK_N: J2.9, U1.2
MUXED1_CLK_P: J2.7, U1.3
MUXED1_D0_N: J2.3, U1.4
MUXED1_D0_P: J2.1, U1.5
MUXED1_D1_N: J2.15, U1.6
MUXED1_D1_P: J2.13, U1.7
MUXED1_D2_N: J2.4, U1.12
MUXED1_D2_P: J2.2, U1.11
MUXED1_D3_N: J2.16, U1.14
MUXED1_D3_P: J2.14, U1.13
MUXED2_CLK_N: J2.27, U4.4
MUXED2_CLK_P: J2.25, U4.5
MUXED2_D0_N: J2.21, U4.6
MUXED2_D0_P: J2.19, U4.7
MUXED2_D1_N: J2.33, U4.11
MUXED2_D1_P: J2.31, U4.12
MUXED2_D2_N: J2.22, U4.13
MUXED2_D2_P: J2.20, U4.14
unnamed: JP1.2, R77.2
unnamed: JP2.2, R78.1
unnamed: JP3.2, R79.1
unnamed: R36.2, U6.1
unnamed: R37.2, U6.24
unnamed: R66.2, U1.8
unnamed: R67.2, U4.8
unnamed: R68.2, U2.14
unnamed: R70.2, U2.13
unnamed: R72.1, U2.37
unnamed: R73.1, U2.32, U2.33, U2.34, U2.35, U2.38
unnamed: R74.1, U2.36
Switch1_SEL1: U1.9, U7.44
Switch1_SEL2: U1.10, U7.43
Switch2_SEL1: U4.9, U7.47
Switch2_SEL2: U4.10, U7.46
VOLT_2P5: JP3.1, R3.2, R4.2, R9.2, R10.2, R15.2, R16.2, R21.2, R22.2, R27.2, R28.2, R38.2, R39.2, R44.2, R45.2, R50.2, R51.2, R56.2, R57.2

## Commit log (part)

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2017-08-01 Initial commit of v1 prototype
2021-09-13 roadmap 2021
2021-09-13 baseline for version 2
2021-09-13 starting from 0
2021-09-16 re-organizing folder structure
2021-09-16 adding footprint libraries
2021-11-13 adding lvds to slvs
2021-11-26 just commit
2021-11-26 just commit2
2021-12-05 Good, before replacing the swithches to TI ones
2021-12-11 good, added re-driver
2021-12-11 good, before reducing
2022-10-20 before re-arranging
2022-10-23 rev 2022
2022-10-23 minor changes
2022-10-23 good, before completely removing redriver part
2022-10-25 fixed 3.3 volt level shifter
2022-10-28 added EEPROM
2022-10-29 added more level shifters and power 1.8 Volt
2022-11-01 minor changes 4
2022-11-01 adding power supplies
2022-11-01 adding more power supplies
2022-11-01 populating FMC connector
2022-11-01 cleanup 3D shapes
2022-11-03 Adding more LVDS lines
2022-11-05 added 4 bit level shifter VADJ to 3.3 volt
2022-11-05 removed unused components
2022-11-10 added enable line for slow signals
2022-11-11 Finished initial placement
2022-11-11 minor changes in positions
2022-11-12 placed nicely the components
2022-11-13 good, before FMC lines connect
2022-11-13 Added dummy nets to FMC connector
2022-11-17 started routing
2022-11-22 before hi-speed routing
2022-11-22 converted to Kicad6
2022-11-25 started to route high-speed lanes
2022-11-25 more routing
2022-11-25 added gitignore
2022-11-25 a little cleanup
2022-11-25 removed redundunt ground planes from
2022-11-26 good, before HS length tuning
2022-12-03 DRC, ERC OK
2022-12-03 All warnings fixed
2022-12-03 Ready for BOM and Gerbers
2022-12-03 Added manufacturing to gitignore
2022-12-05 Added BOM to gitignore
2022-12-06 JLCPCB BOM OK
2022-12-10 All DRC, ERC and BOM are good
2022-12-18 Added debug points
2022-12-19 Added debug connector
2022-12-19 Generated BOM, before Gerbers generation
2022-12-19 generated gerbers and BOMs
2023-02-28 updated readme2
